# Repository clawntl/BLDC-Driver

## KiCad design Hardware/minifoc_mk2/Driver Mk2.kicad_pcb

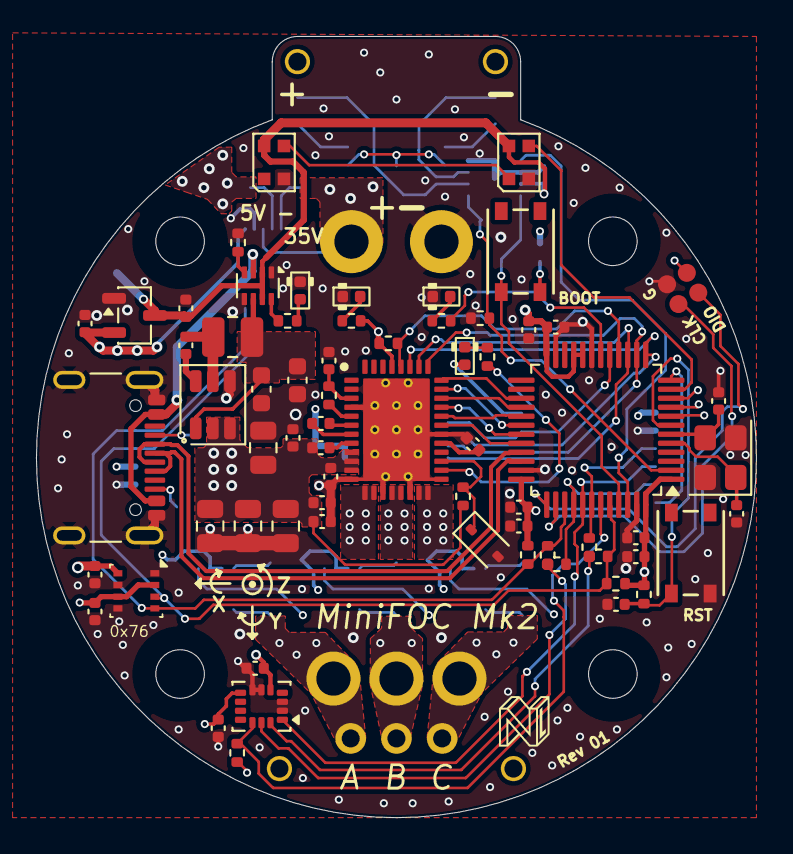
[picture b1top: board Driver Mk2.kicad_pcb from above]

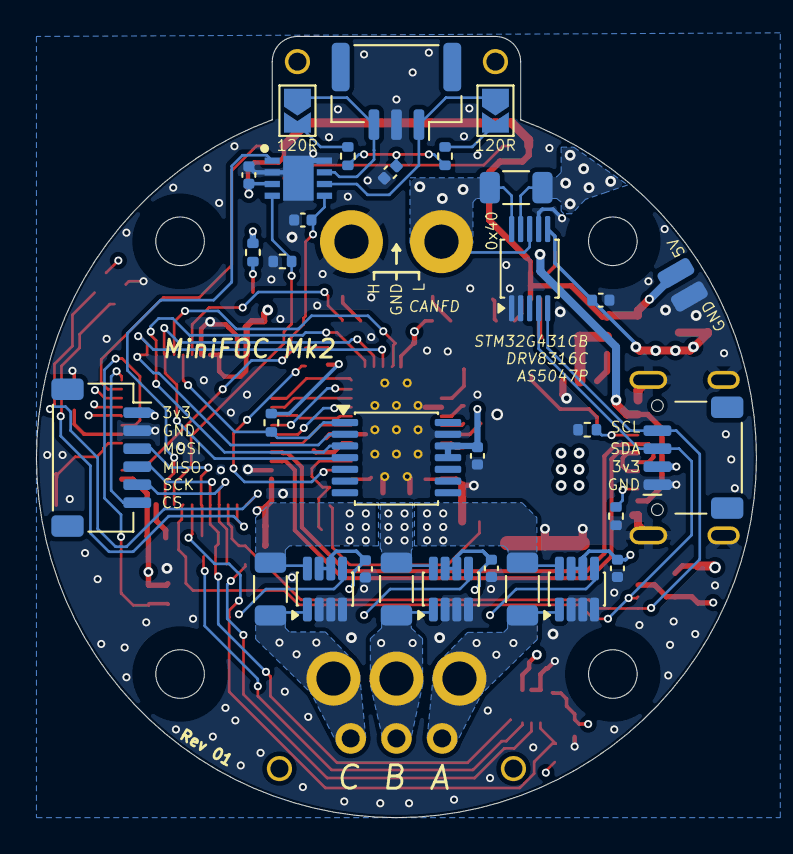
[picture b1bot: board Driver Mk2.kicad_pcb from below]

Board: 4 copper layers, 40.0 x 43.4 mm, 103 parts (31 on the bottom side), 73 nets.

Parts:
C1, C5, C6, C7, C9, C11, C13, C15, C16, C19, C20, C30, C31, C32, C35, C40, C41, C48: 100nF; C_0402_1005Metric
C8, C10, C12, C17, C18, C21, C22, C25, C26: 1uF; C_0402_1005Metric
C14: 22uF; C_0402_1005Metric
C23: 47nF; C_0402_1005Metric
C24: 4.7uF; C_0402_1005Metric
C33, C34: 10pF; C_0402_1005Metric
C36, C37, C38, C49: 10uF; C_0805_2012Metric
C39, C47: 22uF; C_0603_1608Metric
D1, D2, D7: ORANGE; LED_0402_1005Metric
D3, D5: WS2812B-2020; LED_WS2812B-2020_PLCC4_2.0x2.0mm
D6: BZT52B5V1S; D_SOD-323
D8: BLUE; LED_0402_1005Metric
H1, H2, H3, H4: MountingHole; MountingHole_2.7mm_M2.5_DIN965
IC1: LSM6DSV16XTR; LSM6DSV16BXTR
IC2: LM66200DRLR; SOT-583-8
J1: USB_C_Receptacle_USB2.0_16P; USB_C_Receptacle_GCT_USB4105-xx-A_16P_TopMnt_Horizontal
J2: MR30 Phase; AMASS_MR30PW-FB_1x03_P3.50mm_Horizontal
J3: Dupont 2.54 Phase; PinHeader_1x03_P2.54mm_Horizontal
J4: XT30PW-M; AMASS_XT30PW-M
J5: SPI3 Conn; JST_SH_SM06B-SRSS-TB_1x06-1MP_P1.00mm_Horizontal
J6: Conn_02x02_Odd_Even; DebugHeader2x02_P1.27mm
J7: CAN Conn; JST_GH_SM03B-GHS-TB_1x03-1MP_P1.25mm_Horizontal
J8: Conn_01x04_MountingPin; JST_SH_SM04B-SRSS-TB_1x04-1MP_P1.00mm_Horizontal
J9: Conn_01x02; SolderWirePad_1x02_SMD_1x2mm
JP1, JP2: CAN Term1; SolderJumper-2_P1.3mm_Open_TrianglePad1.0x1.5mm
JP3, JP4: SolderJumper_3_Open; Resistor 2 Position 90deg 0402
L2: 4.7uH; L_1008_2520Metric
R1, R4, R8, R17: 3m ±1%; R_1206_3216Metric
R2, R3, R9, R10, R24: 5.1k; R_0402_1005Metric
R5, R14, R15, R16, R18, R21, R23: 10k; R_0402_1005Metric
R6, R7: 4.7k; R_0402_1005Metric
R12, R13: 60.4R; R_0402_1005Metric
R19, R22: 330R; R_0402_1005Metric
R20: 100k; R_0402_1005Metric
R27: 22R; R_0402_1005Metric
SW1, SW2: PTS815SJM250SMTR LFS; PTS815SJM250SMTRLFS
U1, U11, U12: INA241A3IDDFR; SOT-23-8
U3: BME280; Bosch_LGA-8_2.5x2.5mm_P0.65mm_ClockwisePinNumbering
U4: ATA6561-GBQW-N
U5: STM32G431CBT6; LQFP-48_7x7mm_P0.5mm
U6: AS5047P; TSSOP-14_4.4x5mm_P0.65mm
U7: DRV8316CRRGFR
U8: AP63205WU; TSOT-23-6
U13: INA226; VSSOP-10_3x3mm_P0.5mm
U14: XC6206P332MR-G; SOT-23-3
Y3: 16 MHz; Crystal_SMD_3225-4Pin_3.2x2.5mm

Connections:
+3V3: C1.1, C5.1, C8.1, C9.1, C10.1, C11.1, C12.1, C13.1, C15.1, C16.1, C26.1, C30.1, C31.1, C35.1, C40.1, C41.1, D1.2 (A), IC1.5 (VDD_IO), IC1.8 (VDD), J5.1, J6.3, J8.2, R6.2, R7.2, R10.2, R15.1, R16.1, R18.1, R21.1, R22.1, U1.6 (V+), U1.7 (REF1), U3.2 (CSB), U3.6 (VDDIO), U3.8 (VDD), U5.1 (VBAT), U5.20 (VREF+), U5.21 (VDDA), U5.24 (VDD), U5.36 (VDD), U5.48 (VDD), U6.11 (VDD), U6.12 (VDD3V3), U7.37 (VREF/_ILIM), U11.6 (V+), U11.7 (REF1), U12.6 (V+), U12.7 (REF1), U13.6 (VS), U14.2 (VO)
+5V: C6.1, C25.1, D3.4 (VDD), D5.4 (VDD), IC2.2 (VOUT), IC2.7 (VOUT), J9.1, U4.3 (VCC), U14.3 (VI)
+5V_BUCK: C39.1, C47.1, IC2.6 (VIN2), L2.2, U8.1 (FB)
+DRV_BUCK: C14.1, R27.1, U7.3 (FB_BK)
/CAN_H: J7.3, JP1.1 (A), U4.7 (CANH)
/CAN_L: J7.1, JP2.1 (A), U4.6 (CANL)
/CAN_RX/BOOT0: R23.1, SW2.1, U4.4 (RXD), U5.45 (PB8)
/CAN_TX: U4.1 (TXD), U5.46 (PB9)
/CAN_VIO: C7.1, R5.2, U4.5 (VIO), U5.2 (PC13)
/DRV_CS: R15.2, U5.16 (PB0), U7.36 (NSCS)
/DRV_HA: U5.32 (PA10), U7.27 (INHA)
/DRV_HB: U5.31 (PA9), U7.29 (INHB)
/DRV_HC: U5.30 (PA8), U7.31 (INHC)
/DRV_LA: U5.29 (PB15), U7.28 (INLA)
/DRV_LB: U5.28 (PB14), U7.30 (INLB)
/DRV_LC: U5.27 (PB13), U7.32 (INLC)
/ENC_CS: R16.2, U5.17 (PB1), U6.1 (~CS)
/I2C1_SCL: J8.4, JP3.3 (B), R7.1, U3.4 (SCK), U5.39 (PA15), U13.5 (SCL)
/I2C1_SDA: J8.3, JP4.1 (A), R6.1, U3.3 (SDI), U5.44 (PB7), U13.4 (SDA)
/IMU_CS: IC1.12 (CS), R18.2, U5.43 (PB6)
/NRST: C32.1, R21.2, SW1.1, U5.7 (PG10)
/OUT_1: R4.1, U1.8 (+), U7.13 (OUTA_1), U7.14 (OUTA_2)
/OUT_2: R8.1, U7.16 (OUTB_1), U7.17 (OUTB_2), U11.8 (+)
/OUT_3: R17.1, U7.19 (OUTC_1), U7.20 (OUTC_2), U12.8 (+)
/OUT_A: J2.1, J3.3, R4.2, U1.1 (-)
/OUT_B: J2.2, J3.2, R8.2, U11.1 (-)
/OUT_C: J2.3, J3.1, R17.2, U12.1 (-)
/RGB_LED: D5.3 (DIN), U5.11 (PA3)
/SOA: U1.5, U5.10 (PA2)
/SOB: U5.9 (PA1), U11.5
/SOC: U5.8 (PA0), U12.5
/SP1_MISO: U5.14 (PA6), U6.3 (MISO), U7.33 (SDO)
/SP1_MOSI: U5.15 (PA7), U6.4 (MOSI), U7.34 (SDI)
/SP1_SCK: U5.13 (PA5), U6.2 (CLK), U7.35 (SCLK)
/SP3_MISO: IC1.1 (SDO/SA0), J5.4, U5.41 (PB4)
/SP3_MOSI: J5.3, JP4.3 (B), U5.42 (PB5)
/SP3_NSS: J5.6, U5.12 (PA4)
/SP3_SCK: J5.5, JP3.1 (A), U5.40 (PB3)
/SWCLK: J6.2, U5.38 (PA14)
/SWDIO: J6.1, U5.37 (PA13)
/SW_BK: R27.2, U7.5 (SW_BK)
/USB_D_N: J1.A7 (D-), J1.B7 (D-), U5.33 (PA11)
/USB_D_P: J1.A6 (D+), J1.B6 (D+), U5.34 (PA12)
/USER LED: R19.2, U5.18 (PB2)
/XTAL_IN: C33.2, U5.5 (PF0), Y3.1
/XTAL_OUT: C34.1, U5.6 (PF1), Y3.3
GND: C1.2, C5.2, C6.2, C7.2, C8.2, C9.2, C10.2, C11.2, C12.2, C13.2, C14.2, C15.2, C16.2, C18.2, C19.2, C20.2, C21.2, C22.2, C24.2, C25.2, C26.2, C30.2, C31.2, C32.2, C33.1, C34.2, C35.2, C36.2, C37.2, C38.2, C39.2, C40.2, C41.2, C47.2, C49.2, D2.1 (K), D3.2 (VSS), D5.2 (VSS), D6.2 (A), D7.1 (K), D8.1 (K), IC1.2 (SDX/AH1/QVAR1), IC1.3 (SCX/AH2/QVAR2), IC1.6 (GND_1), IC1.7 (GND_2), IC2.1 (GND_1), IC2.5 (GND_2), J1.A1 (GND), J1.A12 (GND), J1.B1 (GND), J1.B12 (GND), J1.S1 (SHIELD), J4.1, J5.2, J6.4, J7.2, J8.1, J9.2, R2.1, R3.1, R5.1, R14.2, R23.2, SW1.3, U1.2 (GND), U1.3 (REF2), U1.4 (GND), U3.1 (GND), U3.5 (SDO), U3.7 (GND), U4.2 (GND), U4.8 (STBY), U4.9 (EP), U5.19 (VSSA), U5.23 (VSS), U5.35 (VSS), U5.47 (VSS), U6.13 (GND), U7.2 (AGND_1), U7.4 (GND_BK), U7.12 (PGND_1), U7.15 (PGND_2), U7.18 (PGND_3), U7.21 (DRVOFF), U7.26 (AGND_2), U7.41 (EP), U8.4 (GND), U11.2 (GND), U11.3 (REF2), U11.4 (GND), U12.2 (GND), U12.3 (REF2), U12.4 (GND), U13.1 (A1), U13.2 (A0), U13.7 (GND), U14.1 (GND), Y3.2, Y3.4
unnamed: C24.1, R12.2, R13.1
unnamed: D1.1 (K), R9.1
unnamed: D2.2 (A), R24.1
unnamed: D3.3 (DIN), D5.1 (DOUT)
unnamed: D6.1 (K), R20.2, U7.23 (NSLEEP)
unnamed: D7.2 (A), R19.1
unnamed: D8.2 (A), R10.1
unnamed: IC1.13 (SCL/SCK), JP3.2 (C)
unnamed: IC1.14 (SDA/MOSI), JP4.2 (C)
unnamed: IC2.8 (ST), R24.2
unnamed: IC2.4 (~ON), R14.1
unnamed: J1.A5 (CC1), R2.2
unnamed: J1.B5 (CC2), R3.2
unnamed: JP1.2 (B), R12.1
unnamed: JP2.2 (B), R13.2
unnamed: R22.2, SW2.3
unnamed: C18.1, U7.25 (AVDD)
unnamed: C17.1, U7.8 (CP)
unnamed: C23.2, U7.7 (CPH)
unnamed: C23.1, U7.6 (CPL)
unnamed: R9.2, U7.22 (NFAULT)
unnamed: C48.2, U8.6 (BST)
unnamed: C48.1, L2.1, U8.5 (SW)
V_IN: J4.2, R1.1, U13.8 (Vbus), U13.10 (Vin+)
V_M: C17.2, C19.1, C20.1, C21.1, C22.1, C36.1, C37.1, C38.1, C49.1, R1.2, R20.1, U7.9 (VM_1), U7.10 (VM_2), U7.11 (VM_3), U8.2 (EN), U8.3 (IN), U13.9 (Vin-)
V_USB: IC2.3 (VIN1), J1.A4 (VBUS), J1.A9 (VBUS), J1.B4 (VBUS), J1.B9 (VBUS)

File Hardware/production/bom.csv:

Designator,Footprint,Quantity,Value,LCSC Part #
"C1, C11, C13, C15, C16, C19, C20, C30, C31, C32, C35, C40, C41, C48, C5, C6, C7, C9",0402,18,100nF,C85858
"C10, C12, C17, C18, C25, C26, C8",0402,7,1uF,C52923
C14,0402,1,22uF,C3845593
"C21, C22",0402,2,1uF,C1518208
C23,0402,1,47nF,C307339
C24,0402,1,4.7uF,C368809
"C33, C34",0402,2,10pF,C32949
"C36, C37, C38, C49",0805,4,10uF,C440198
"C39, C47",0603,2,22uF,C59461
"D1, D2, D7",0402,3,ORANGE,C965791
"D3, D5",LED_WS2812B-2020_PLCC4_2.0x2.0mm,2,WS2812B-2020,C965555
D6,D_SOD-323,1,BZT52B5V1S,C5261067
D8,0402,1,BLUE,C42436699
IC1,LSM6DSV16BXTR,1,LSM6DSV16XTR,C5267406
IC2,SOT-583-8,1,LM66200DRLR,C3235556
J1,USB_C_Receptacle_GCT_USB4105-xx-A_16P_TopMnt_Horizontal,1,USB_C_Receptacle_USB2.0_16P,C2765186
J4,AMASS_XT30PW-M,1,XT30PW-M,C431092
J5,JST_SH_SM06B-SRSS-TB_1x06-1MP_P1.00mm_Horizontal,1,SPI3 Conn,C160405
J7,JST_GH_SM03B-GHS-TB_1x03-1MP_P1.25mm_Horizontal,1,CAN Conn,C22472755
J8,JST_SH_SM04B-SRSS-TB_1x04-1MP_P1.00mm_Horizontal,1,Conn_01x04_MountingPin,C160404
L2,1008,1,4.7uH,C5832360
"R1, R17, R4, R8",1206,4,3m ±1%,C20608716
"R10, R2, R24, R3, R9",0402,5,5.1k,C25905
"R12, R13",0402,2,60.4R,C137954
"R14, R15, R16, R18, R21, R23, R5",0402,7,10k,C25744
"R19, R22",0402,2,330R,C25104
R20,0402,1,100k,C25741
R27,0402,1,22R,C114765
"R6, R7",0402,2,4.7k,C25900
"SW1, SW2",PTS815SJM250SMTRLFS,2,PTS815SJM250SMTR LFS,C2689510
"U1, U11, U12",SOT-23-8,3,INA241A3IDDFR,C6051860
U13,VSSOP-10_3x3mm_P0.5mm,1,INA226,C49851
U14,SOT-23-3,1,XC6206P332MR-G,C5446
U3,Bosch_LGA-8_2.5x2.5mm_P0.65mm_ClockwisePinNumbering,1,BME280,C92489
U4,ATA6561-GBQW-N,1,ATA6561-GBQW-N,C617297
U5,LQFP-48_7x7mm_P0.5mm,1,STM32G431CBT6,C529355
U6,TSSOP-14_4.4x5mm_P0.65mm,1,AS5047P,C962063
U7,DRV8316CRRGFR,1,DRV8316CRRGFR,C5447274
U8,TSOT-23-6,1,AP63205WU,C2071056
Y3,Crystal_SMD_3225-4Pin_3.2x2.5mm,1,16 MHz,C13738
